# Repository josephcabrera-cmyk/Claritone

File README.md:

# Claritone

A head-mounted navigation aid for visually impaired users. Time-of-flight (ToF) sensors measure how far away obstacles are, and the device turns that distance into audio cues. The full design adds camera-based object detection and spatial audio. [Status at the showcase](#status-at-the-showcase) covers what actually ran.

Developed as a senior design project (ESE440/ESE441) at Stony Brook University, Fall 2025 – Spring 2026.

## Status at the showcase

**What ran:** the front VL53L7CX sensor drove an audio tone through both speakers. Closer obstacles sound higher, pulse faster and play louder. The user can pick one of three sensitivity ranges (0.3, 0.8 or 1.5 m) and three tone presets, and set volume or mute with the scroll wheel. This is [`firmware/Claritone_L7_Audio`](firmware/Claritone_L7_Audio).

**Designed but not finished:**

- **Side and rear sensors:** the firmware supports four sensors, but only the front one came online.
- **Spatial audio:** Sola's engine (panning, head shadow and interaural delay) is ported to the board in [`firmware/Claritone_Main`](firmware/Claritone_Main). With only the front sensor working, it had no direction to place a sound in.
- **Object detection:** the camera and computer vision work was developed separately in the [team repository](https://github.com/Niefr1/Blindsight-Claritone-Senior-Design) and wasn't combined with the ToF and audio firmware.
- **Battery-saving polling:** the plan was to run every sensor at a low rate and switch the front sensor to high-rate ranging when the camera flags a target.

## System design

The full design runs object detection on the STM32N6's Neural-ART NPU and pairs it with multizone ToF ranging:

1. A pre-trained model from ST's Model Zoo flags a region of interest in the camera frame.
2. The ToF sensors measure how far away that object is.
3. A spatial audio engine places a tone in the obstacle's direction, using equal-power panning, interaural time delay and distance attenuation.

## Hardware

**Custom PCB (Claritone Main Board)**

| Parameter | Value |
|---|---|
| Dimensions | 110 mm x 41.5 mm |
| Layer count | 4-layer FR-4 |
| MCU | STM32N657X0H3Q (Cortex-M55 + Neural-ART NPU, VFBGA-264) |
| ToF sensors | 1x VL53L7CX on-board + 3x SATEL-VL53L7CX breakouts via JST-GH |
| Camera | Arducam IMX335 via 15-pin MIPI CSI FPC connector |
| Audio output | 2x MAX98357A I2S Class-D amplifiers (stereo) |
| Power | 2x 3000 mAh LiPo cells in parallel, MCP73831T charge management, TPS62132 buck (3.3V), TPS7A2018 LDO (1.8V) |
| Protection | Battery reverse-polarity P-MOSFET (DMG2301L), resettable polyfuse (MF-PSMF075X), SD05 TVS diode, USBLC6-2SC6 ESD protection on Micro-USB |
| Charging | Micro-USB (power only) |
| Storage | MicroSD via SDMMC1 |
| Debug | STLINK-V3MINIE via STDC14 header (SWD + VCP) |
| Fabrication | JLCPCB (4-layer, ENIG finish) |

### Schematic

Full schematic PDF: [Claritone_Schematic.pdf](hardware/schematic/Claritone_Schematic.pdf)

### PCB Layout

Full layout PDFs: [Top](hardware/schematic/Claritone_PCB_TOP.pdf) | [Bottom](hardware/schematic/Claritone_PCB_BOTTOM.pdf)

### Design files

The EAGLE 9.7 sources are [`Claritone_Main.sch`](hardware/source/Claritone_Main.sch) and [`Claritone_Main.brd`](hardware/source/Claritone_Main.brd). They open in Autodesk EAGLE 9.7 or later and in Fusion Electronics.

### Bill of materials

[`hardware/bom/claritone-bom.csv`](hardware/bom/claritone-bom.csv) lists every part with a one-line design note ([`.xlsx`](hardware/bom/claritone-bom.xlsx) version).

## Firmware

[`firmware/`](firmware) holds one STM32CubeIDE project per bring-up step, from a pin-toggle test (L0) to the combined program (L8), plus `Claritone_Main`. L7 is the showcase build. [`firmware/README.md`](firmware/README.md) explains what each project does and how to build it.

[`prototypes/spatial-audio`](prototypes/spatial-audio) is Sola's desktop prototype of the spatial audio engine.

## Folder Structure

```
Claritone/
├── firmware/                 # STM32N657 sources and .ioc files
│   ├── Claritone_L0_Blinky/  # bring-up steps L0–L8, one project each
│   ├── ...
│   ├── Claritone_L7_Audio/   # showcase build
│   ├── Claritone_L8_Integration/
│   ├── Claritone_Main/       # spatial audio engine and UI
│   └── claritone-board.ioc   # board pin and peripheral configuration
├── prototypes/
│   └── spatial-audio/        # desktop spatial audio prototype
├── hardware/
│   ├── source/               # EAGLE schematic and board files
│   ├── schematic/            # schematic and layout PDFs and images
│   └── bom/                  # bill of materials
├── docs/
│   └── images/               # photo, renders, block diagram
└── README.md
```

## Building and Flashing

### Requirements
- STM32CubeMX and STM32CubeIDE
- STM32CubeProgrammer (CLI recommended for STM32N6)
- STLINK-V3MINIE debugger (firmware V3J17M10 or later)

### Steps
1. Generate each project's code from its `.ioc` in STM32CubeMX, then add ST's VL53L7CX ULD driver ([details](firmware/README.md#building))
2. Build the FSBL sub-project first
3. Build the Appli sub-project
4. Flash via SWD using STM32CubeProgrammer CLI

> **Note:** The STM32N657 requires dev boot mode (BOOT1 high) for SRAM write access and debug. On the custom PCB, DIP switch SW1 sets BOOT0 and BOOT1. BOOT1 is PA6, with a 10 kΩ pulldown (R46).

## Team

Built by a three-person team at Stony Brook University:

- **[Joseph Cabrera](https://github.com/josephcabrera-cmyk)**: schematic and 4-layer PCB design, board bring-up, ToF sensing architecture, the distance-to-tone mapping in the showcase build, and enclosure design
- **Sola**: the spatial audio engine
- **Joseph** and **Sola**: firmware
- **Felix** and **Sola**: computer vision model selection and deployment on the Neural-ART NPU

The full project, including the computer vision work, is in the [team repository](https://github.com/Niefr1/Blindsight-Claritone-Senior-Design).

## License

This project was developed for academic purposes. The VL53L7CX ULD driver (STSW-IMG036) is not included in this repository due to ST redistribution restrictions. ST's HAL and CMSIS are left out too, since STM32CubeMX regenerates them from each `.ioc`.

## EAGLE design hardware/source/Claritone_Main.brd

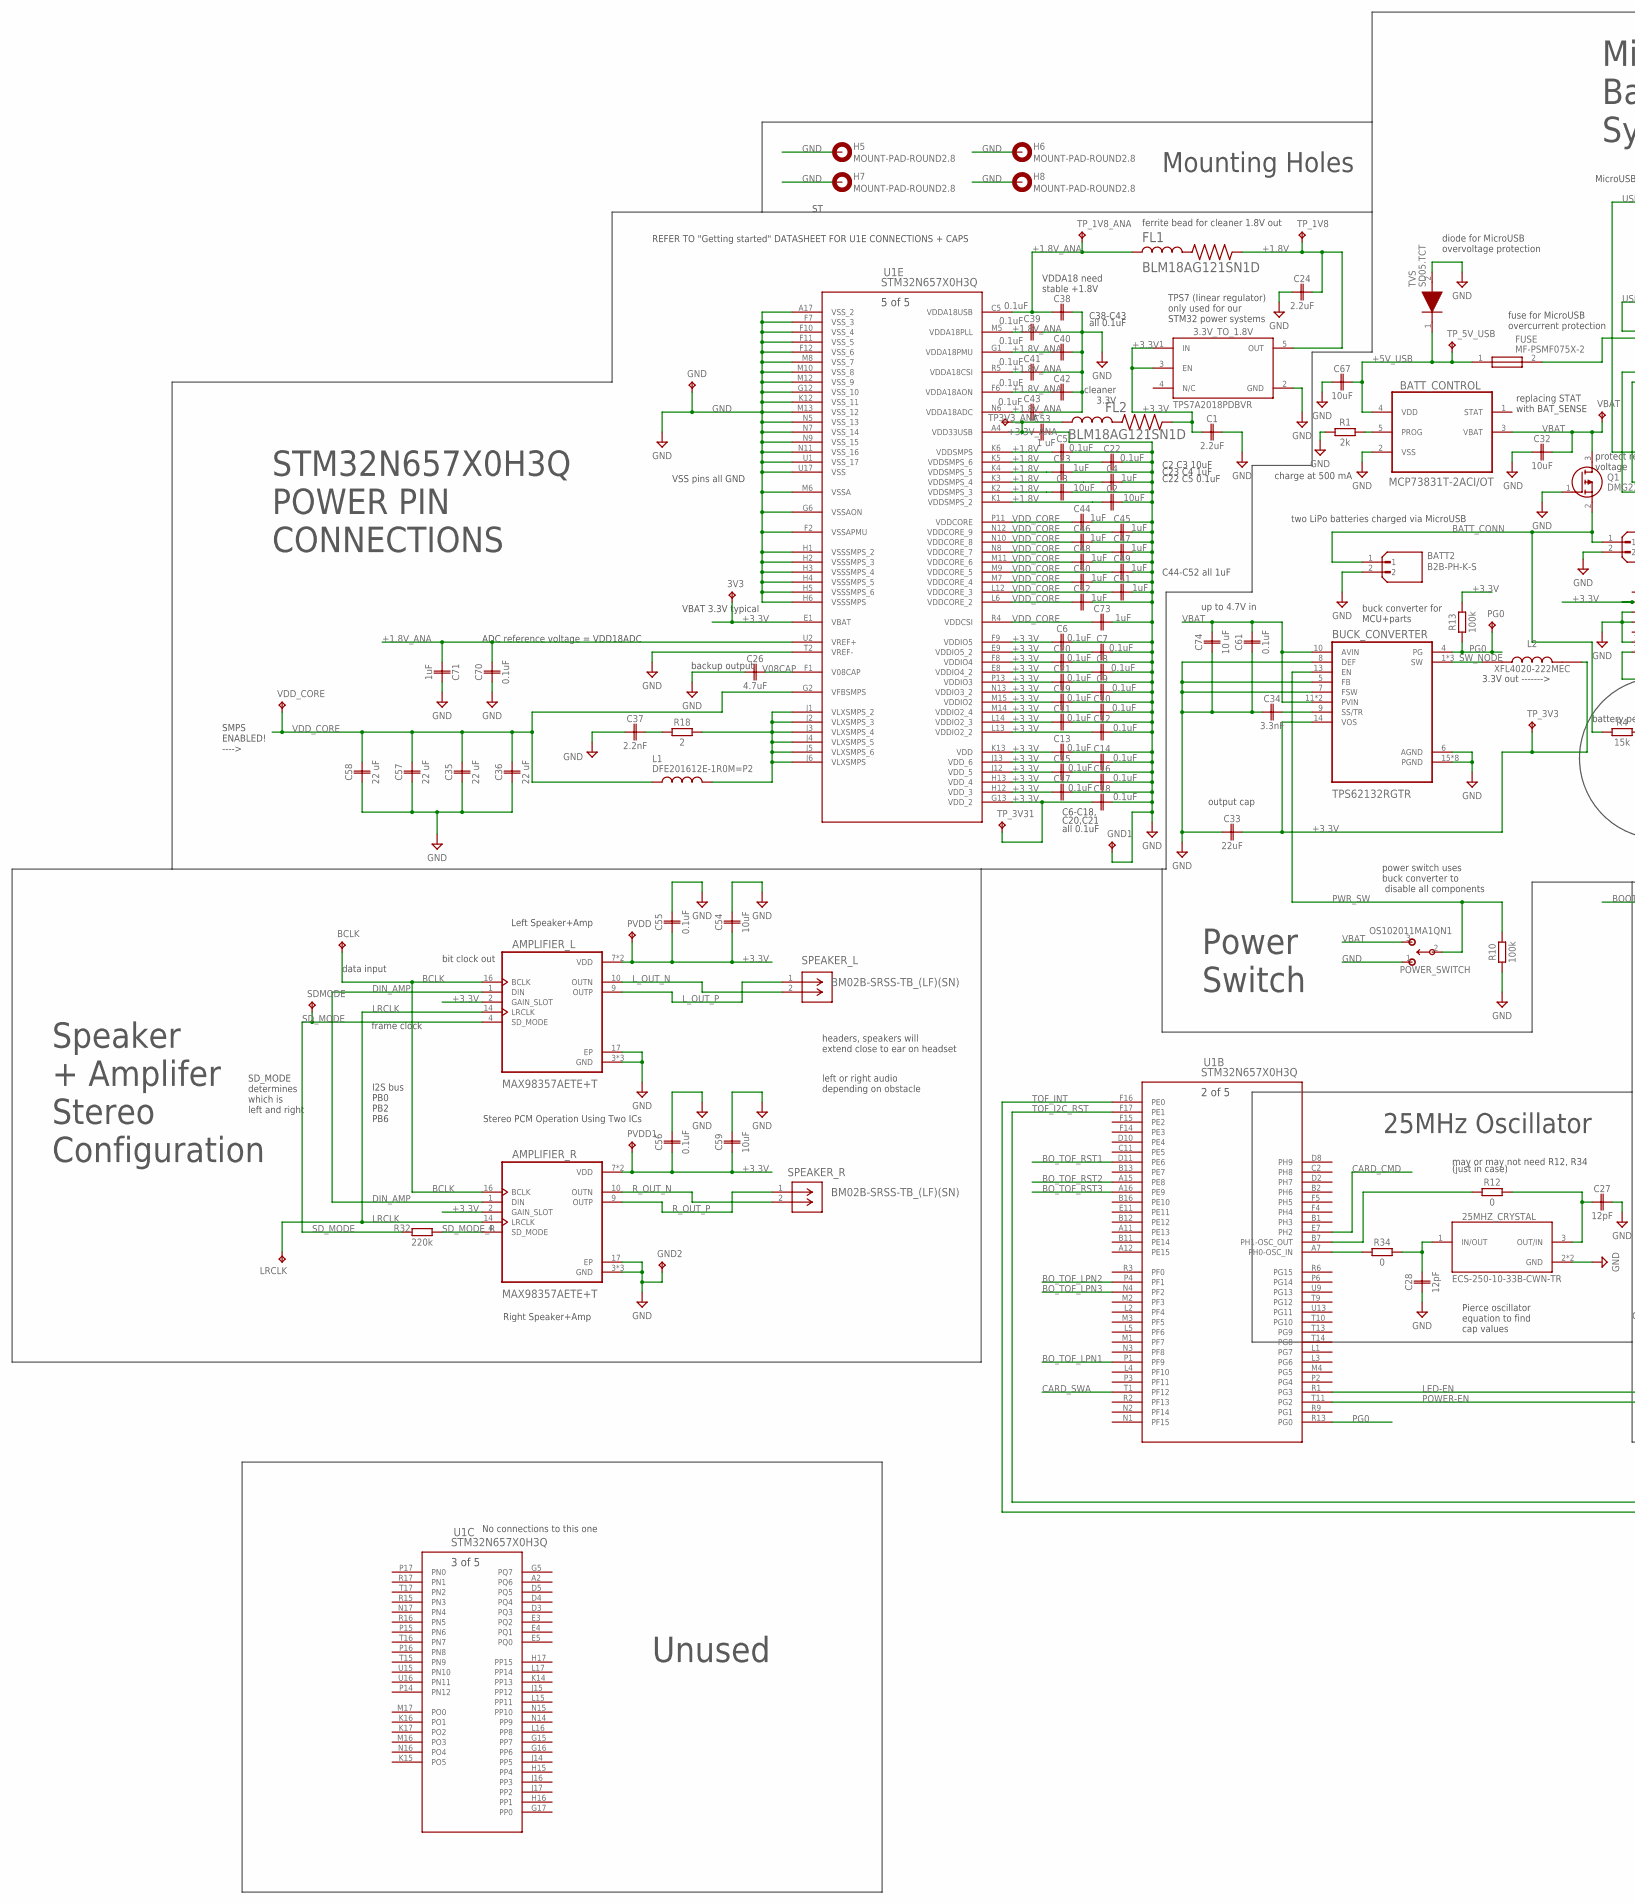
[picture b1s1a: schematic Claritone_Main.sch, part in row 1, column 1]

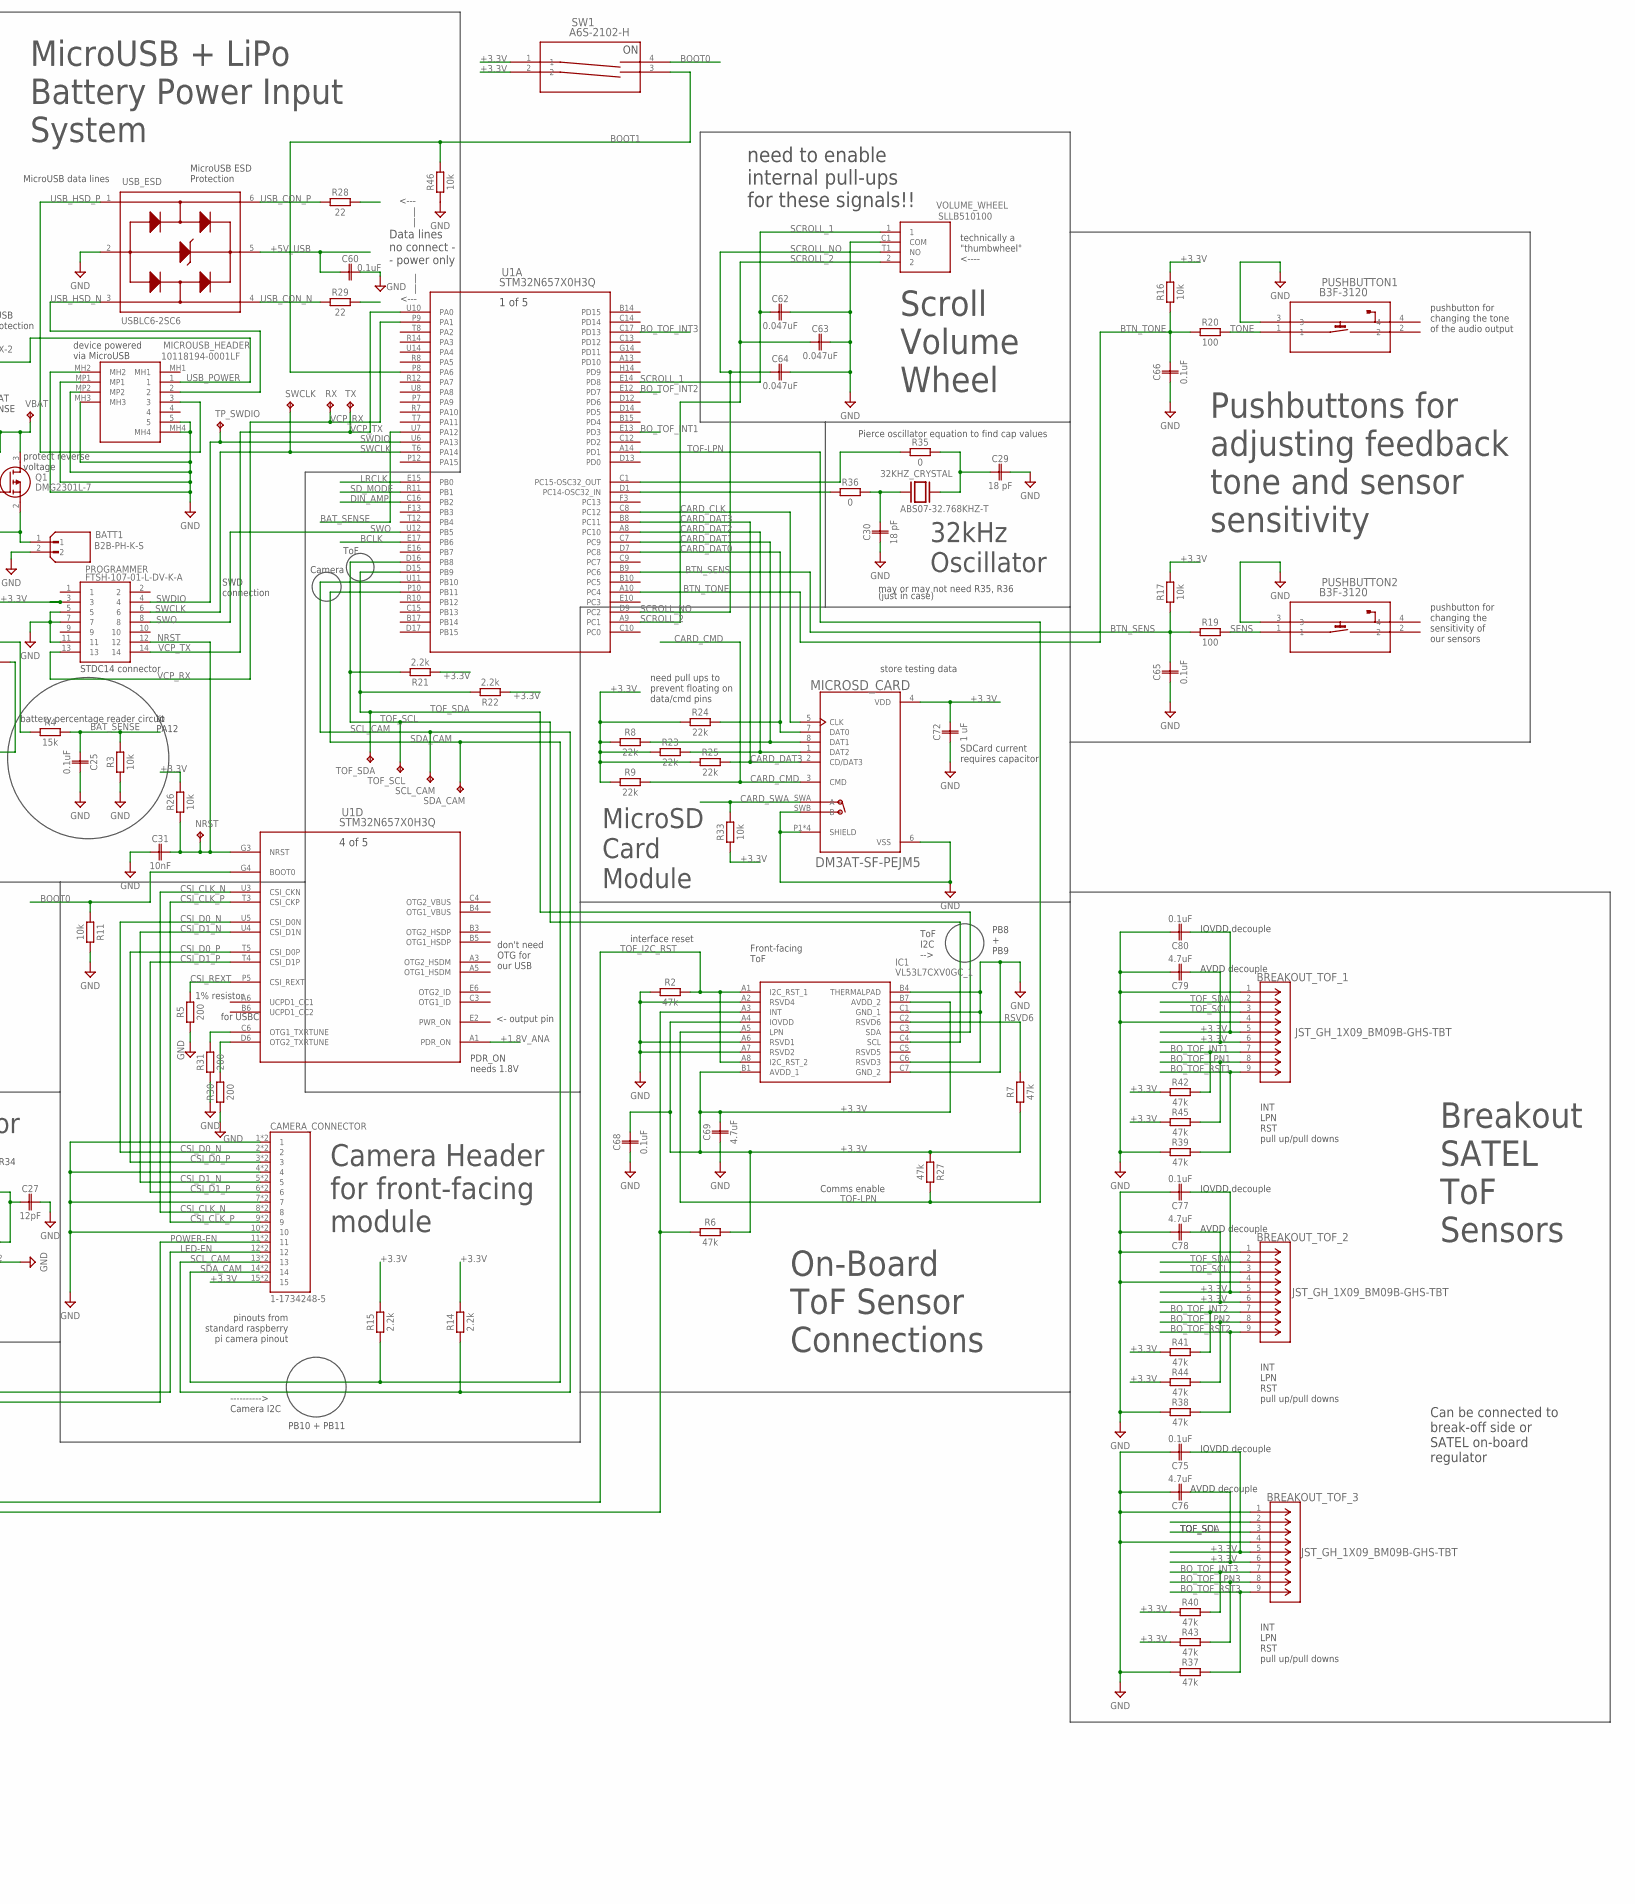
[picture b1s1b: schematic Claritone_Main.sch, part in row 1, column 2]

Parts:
3.3V_TO_1.8V: TPS7A2018PDBVR; SOT95P280X145-5N(3)
3V3: TPPAD1-13Y; P1-13Y
25MHZ_CRYSTAL: ECS-250-10-33B-CWN-TR; XTAL_ECS-250-10-33B-CWN-TR
32KHZ_CRYSTAL: ABS07-32.768KHZ-T; XTAL_ABS07-32.768KHZ-T
AMPLIFIER_L: MAX98357AETE+T; QFN50P300X300X80-17N
AMPLIFIER_R: MAX98357AETE+T; QFN50P300X300X80-17N
BATT1, BATT2: B2B-PH-K-S; JST_B2B-PH-K-S
BATT_CONTROL: MCP73831T-2ACI/OT; SOT95P280X145-5N(1)
BCLK: TPTP06R; TP06R
BREAKOUT_TOF_1, BREAKOUT_TOF_2, BREAKOUT_TOF_3: JST_GH_1X09_BM09B-GHS-TBT; CONN_BM09B-GHS-TBT_JST
BUCK_CONVERTER: TPS62132RGTR; QFN50P300X300X100-17N
C1, C24: 2.2uF; CAPC1005X60
C2, C3, C32, C54, C59, C67: 10uF; CAPC1608X85
C4, C23, C44, C45, C46, C47, C48, C49, C50, C51, C52, C71, C73: 1uF; CAPC1005X60
C5, C6, C7, C8, C9, C10, C11, C12, C13, C14, C15, C16, C17, C18, C19, C20, C21, C22, C25, C38, C39, C40, C41, C42, C43, C55, C56, C60, C61, C65, C66, C68, C70, C75, C77, C80: 0.1uF; CAPC1005X60
C26: 4.7uF; CAPC1005X60
C27, C28: 12pF; CAPC1005X60
C29, C30: 18 pF; CAPC1005X60
C31: 10nF; CAPC1005X60
C33: 22uF; CAPC1608X85
C34: 3.3nF; CAPC1005X60
C35, C36, C57, C58: 22 uF; CAPC1608X85
C37: 2.2nF; CAPC1005X60
C53, C72: 1 uF; CAPC1005X60
C62, C63, C64: 0.047uF; CAPC1005X60
C69, C76, C78, C79: 4.7uF; CAPC1608X85
C74: 10 uF; CAPC1608X85
CAMERA_CONNECTOR: 1-1734248-5; TE_1-1734248-5
FL1, FL2: BLM18AG121SN1D; BEADC1608X95N
FUSE: MF-PSMF075X-2; MFPSMF075X2
GND: TPPAD1-13Y; P1-13Y
GND1, GND2: TPTP08R; TP08R
H5, H6, H7, H8: MOUNT-PAD-ROUND2.8; 2,8-PAD
IC1: VL53L7CXV0GC_1; VL53L7CXV0GC1
L1: DFE201612E-1R0M=P2; INDC2016X120N
L2: XFL4020-222MEC; IND_XFL4020-222MEC
LRCLK: TPTP06R; TP06R
MICROSD_CARD: DM3AT-SF-PEJM5; HRS_DM3AT-SF-PEJM5
MICROUSB_HEADER: 10118194-0001LF; 101181940001LF
NRST: TPTP06R; TP06R
PG0: TPTP06R; TP06R
POWER_SWITCH: OS102011MA1QN1; SWITCH_11MA1QN1
PROGRAMMER: FTSH-107-01-L-DV-K-A; FTSH-107-XX-YYY-DV-K-A
PUSHBUTTON1, PUSHBUTTON2: B3F-3120; SW_B3F-3120_OMR
PVDD, PVDD1: TPTP06R; TP06R
Q1: DMG2301L-7; SOT96P240X115-3N
R1: 2k; RESC1005X40
R2, R6, R7, R27, R37, R38, R39, R40, R41, R42, R43, R44, R45: 47k; RESC1005X40
R3, R11, R16, R17, R26, R33, R46: 10k; RESC1005X40
R4: 15k; RESC1005X40
R5, R30, R31: 200; RESC1005X40
R8, R9, R23, R24, R25: 22k; RESC1005X40
R10, R13: 100k; RESC1005X40
R12, R34, R35, R36: 0; RESC1005X40
R14, R15, R21, R22: 2.2k; RESC1005X40
R18: 2; RESC1005X40
R19, R20: 100; RESC1005X40
R28, R29: 22; RESC1005X40
R32: 220k; RESC1005X40
RX: TPTP06R; TP06R
SCL_CAM: TPTP06R; TP06R
SDA_CAM: TPTP06R; TP06R
SDMODE: TPTP06R; TP06R
SPEAKER_L: BM02B-SRSS-TB_(LF)(SN); CONN_BM02B-SRSS-TB_JST
SPEAKER_R: BM02B-SRSS-TB_(LF)(SN); CONN_BM02B-SRSS-TB_JST
SW1: A6S-2102-H; SW_A6S-2102-H_OMR
SWCLK: TPTP06R; TP06R
TOF_SCL: TPTP06R; TP06R
TOF_SDA: TPTP06R; TP06R
TP3V3_ANA: TPTP06R; TP06R
TP_1V8, TP_1V8_ANA, TP_3V3, TP_3V31, TP_5V_USB: TPTP06R; TP06R
TP_SWDIO: TPTP06R; TP06R
TVS: SD05.TCT; SOD2513X110N
TX: TPTP06R; TP06R
U1: STM32N657X0H3Q; VFBGA264_14X14_STM
USB_ESD: USBLC6-2SC6; SOT95P280X145-6N
VBAT: TPTP06R; TP06R
VDD_CORE: TPTP06R; TP06R
VOLUME_WHEEL: SLLB510100

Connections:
+1.8V: 3.3V_TO_1.8V.5 (OUT), C2.1, C3.1, C4.1, C5.1, C22.1, C23.1, C24.2, FL1.2, TP_1V8.TP, U1.K1 (VDDSMPS_2), U1.K2 (VDDSMPS_3), U1.K3 (VDDSMPS_4), U1.K4 (VDDSMPS_5), U1.K5 (VDDSMPS_6), U1.K6 (VDDSMPS)
+1.8V_ANA: C38.1, C39.1, C40.1, C41.1, C42.1, C43.1, C70.2, C71.1, FL1.1, TP_1V8_ANA.TP, U1.A1 (PDR_ON), U1.C5 (VDDA18USB), U1.F6 (VDDA18AON), U1.G1 (VDDA18PMU), U1.M5 (VDDA18PLL), U1.N6 (VDDA18ADC), U1.R5 (VDDA18CSI), U1.U2 (VREF+)
+3.3V: 3.3V_TO_1.8V.1 (IN), 3.3V_TO_1.8V.3 (EN), 3V3.TP, AMPLIFIER_L.2 (GAIN_SLOT), AMPLIFIER_L.7 (VDD), AMPLIFIER_L.8 (VDD), AMPLIFIER_R.2 (GAIN_SLOT), AMPLIFIER_R.7 (VDD), AMPLIFIER_R.8 (VDD), BREAKOUT_TOF_1.5, BREAKOUT_TOF_1.6, BREAKOUT_TOF_2.5, BREAKOUT_TOF_2.6, BREAKOUT_TOF_3.5, BREAKOUT_TOF_3.6, BUCK_CONVERTER.14 (VOS), C1.1, C6.1, C7.1, C8.1, C9.1, C10.1, C11.1, C12.1, C13.1, C14.1, C15.1, C16.1, C17.1, C18.1, C19.1, C20.1, C21.1, C33.2, C54.1, C55.1, C56.1, C59.1, C68.2, C69.2, C72.2, C75.1, C76.1, C77.1, C78.1, C79.1, C80.1, CAMERA_CONNECTOR.15, CAMERA_CONNECTOR.15_1 (15), FL2.2, IC1.A4 (IOVDD), IC1.B1 (AVDD_1), IC1.B7 (AVDD_2), L2.2, MICROSD_CARD.4 (VDD), PROGRAMMER.3, PVDD.TP, PVDD1.TP, R6.2, R7.1, R8.1, R9.1, R13.2, R14.2, R15.2, R16.2, R17.2, R21.1, R22.1, R23.1, R24.1, R25.1, R26.2, R27.1, R33.1, R40.1, R41.1, R42.1, R43.1, R44.1, R45.1, SW1.1, SW1.2, TP_3V3.TP, TP_3V31.TP, U1.E1 (VBAT), U1.E8 (VDDIO4_2), U1.E9 (VDDIO5_2), U1.F8 (VDDIO4), U1.F9 (VDDIO5), U1.G13 (VDD_2), U1.H12 (VDD_3), U1.H13 (VDD_4), U1.J12 (VDD_5), U1.J13 (VDD_6), U1.K13 (VDD), U1.L13 (VDDIO2_2), U1.L14 (VDDIO2_3), U1.M14 (VDDIO2_4), U1.M15 (VDDIO2), U1.N13 (VDDIO3_2), U1.P13 (VDDIO3)
+3.3V_ANA: C53.1, FL2.1, TP3V3_ANA.TP, U1.A4 (VDD33USB)
+5V_USB: BATT_CONTROL.4 (VDD), C60.1, C67.2, FUSE.1, TP_5V_USB.TP, TVS.1 (K), USB_ESD.5 (VBUS)
BATT_CONN: BATT1.1, BATT2.1, Q1.2 (S), R4.1
BAT_SENSE: C25.1, R3.2, R4.2, U1.U7 (PA12)
BCLK: AMPLIFIER_L.16 (BCLK), AMPLIFIER_R.16 (BCLK), BCLK.TP, U1.E17 (PB6)
BOOT0: R11.1, SW1.4, U1.G4 (BOOT0)
BOOT1: R46.2, SW1.3, U1.P8 (PA6)
BO_TOF_INT1: BREAKOUT_TOF_1.7, R42.2, U1.E13 (PD3)
BO_TOF_INT2: BREAKOUT_TOF_2.7, R41.2, U1.E12 (PD7)
BO_TOF_INT3: BREAKOUT_TOF_3.7, R40.2, U1.C17 (PD13)
BO_TOF_LPN1: BREAKOUT_TOF_1.8, R45.2, U1.P1 (PF9)
BO_TOF_LPN2: BREAKOUT_TOF_2.8, R44.2, U1.P4 (PF1)
BO_TOF_LPN3: BREAKOUT_TOF_3.8, R43.2, U1.N4 (PF2)
BO_TOF_RST1: BREAKOUT_TOF_1.9, R39.2, U1.D11 (PE6)
BO_TOF_RST2: BREAKOUT_TOF_2.9, R38.2, U1.A15 (PE8)
BO_TOF_RST3: BREAKOUT_TOF_3.9, R37.2, U1.A16 (PE9)
BTN_SENS: C65.2, R17.1, R19.1, U1.B9 (PC6)
BTN_TONE: C66.2, R16.1, R20.1, U1.A10 (PC4)
CARD_CLK: MICROSD_CARD.5 (CLK), U1.C8 (PC12)
CARD_CMD: MICROSD_CARD.3 (CMD), R9.2, U1.E7 (PH2)
CARD_DAT0: MICROSD_CARD.7 (DAT0), R24.2, U1.D7 (PC8)
CARD_DAT1: MICROSD_CARD.8 (DAT1), R8.2, U1.C7 (PC9)
CARD_DAT2: MICROSD_CARD.1 (DAT2), R23.2, U1.A8 (PC10)
CARD_DAT3: MICROSD_CARD.2 (CD/DAT3), R25.2, U1.B8 (PC11)
CARD_SWA: MICROSD_CARD.SWA (A), R33.2, U1.T1 (PF12)
CSI_CLK_N: CAMERA_CONNECTOR.8, CAMERA_CONNECTOR.8_1 (8), U1.U3 (CSI_CKN)
CSI_CLK_P: CAMERA_CONNECTOR.9, CAMERA_CONNECTOR.9_1 (9), U1.T3 (CSI_CKP)
CSI_D0_N: CAMERA_CONNECTOR.2, CAMERA_CONNECTOR.2_1 (2), U1.U5 (CSI_D0N)
CSI_D0_P: CAMERA_CONNECTOR.3, CAMERA_CONNECTOR.3_1 (3), U1.T5 (CSI_D0P)
CSI_D1_N: CAMERA_CONNECTOR.5, CAMERA_CONNECTOR.5_1 (5), U1.U4 (CSI_D1N)
CSI_D1_P: CAMERA_CONNECTOR.6, CAMERA_CONNECTOR.6_1 (6), U1.T4 (CSI_D1P)
CSI_REXT: R5.2, U1.P5 (CSI_REXT)
DIN_AMP: AMPLIFIER_L.1 (DIN), AMPLIFIER_R.1 (DIN), U1.C16 (PB2)
GND: 3.3V_TO_1.8V.2 (GND), 25MHZ_CRYSTAL.2 (GND), 25MHZ_CRYSTAL.4 (GND), AMPLIFIER_L.3 (GND), AMPLIFIER_L.11 (GND), AMPLIFIER_L.15 (GND), AMPLIFIER_L.17 (EP), AMPLIFIER_R.3 (GND), AMPLIFIER_R.11 (GND), AMPLIFIER_R.15 (GND), AMPLIFIER_R.17 (EP), BATT1.2, BATT2.2, BATT_CONTROL.2 (VSS), BREAKOUT_TOF_1.1, BREAKOUT_TOF_1.4, BREAKOUT_TOF_2.1, BREAKOUT_TOF_2.4, BREAKOUT_TOF_3.1, BREAKOUT_TOF_3.4, BUCK_CONVERTER.5 (FB), BUCK_CONVERTER.6 (AGND), BUCK_CONVERTER.7 (FSW), BUCK_CONVERTER.8 (DEF), BUCK_CONVERTER.15 (PGND), BUCK_CONVERTER.16 (PGND), BUCK_CONVERTER.17 (PGND), BUCK_CONVERTER.18 (PGND), BUCK_CONVERTER.19 (PGND), BUCK_CONVERTER.20 (PGND), BUCK_CONVERTER.21 (PGND), BUCK_CONVERTER.22 (PGND), C1.2, C2.2, C3.2, C4.2, C5.2, C6.2, C7.2, C8.2, C9.2, C10.2, C11.2, C12.2, C13.2, C14.2, C15.2, C16.2, C17.2, C18.2, C19.2, C20.2, C21.2, C22.2, C23.2, C24.1, C25.2, C26.1, C27.2, C28.1, C29.2, C30.1, C31.1, C32.1, C33.1, C34.1, C35.1, C36.1, C37.1, C38.2, C39.2, C40.2, C41.2, C42.2, C43.2, C44.2, C45.2, C46.2, C47.2, C48.2, C49.2, C50.2, C51.2, C52.2, C53.2, C54.2, C55.2, C56.2, C57.1, C58.1, C59.2, C60.2, C61.1, C62.2, C63.2, C64.2, C65.1, C66.1, C67.1, C68.1, C69.1, C70.1, C71.2, C72.1, C73.2, C74.1, C75.2, C76.2, C77.2, C78.2, C79.2, C80.2, CAMERA_CONNECTOR.1, CAMERA_CONNECTOR.1_1 (1), CAMERA_CONNECTOR.4, CAMERA_CONNECTOR.4_1 (4), CAMERA_CONNECTOR.7, CAMERA_CONNECTOR.7_1 (7), CAMERA_CONNECTOR.10, CAMERA_CONNECTOR.10_1 (10), GND.TP, GND1.TP, GND2.TP, H5.B2,8, H6.B2,8, H7.B2,8, H8.B2,8, IC1.A2 (RSVD4), IC1.A6 (RSVD1), IC1.A7 (RSVD2), IC1.B4 (THERMALPAD), IC1.C1 (GND_1), IC1.C6 (RSVD3), IC1.C7 (GND_2), MICROSD_CARD.6 (VSS), MICROSD_CARD.P1 (SHIELD), MICROSD_CARD.P2 (SHIELD), MICROSD_CARD.P3 (SHIELD), MICROSD_CARD.P4 (SHIELD), MICROSD_CARD.SWB (B), MICROUSB_HEADER.5, MICROUSB_HEADER.MH2, MICROUSB_HEADER.MH3, MICROUSB_HEADER.MH4, MICROUSB_HEADER.MP1, MICROUSB_HEADER.MP2, POWER_SWITCH.1, PROGRAMMER.5, PROGRAMMER.7, PROGRAMMER.11, PUSHBUTTON1.3, PUSHBUTTON2.3, Q1.1 (G), R1.1, R2.1, R3.1, R5.1, R10.1, R11.2, R30.1, R31.1, R37.1, R38.1, R39.1, R46.1, TVS.2 (A), U1.A17 (VSS_2), U1.F2 (VSSAPMU), U1.F7 (VSS_3), U1.F10 (VSS_4), U1.F11 (VSS_5), U1.F12 (VSS_6), U1.G6 (VSSAON), U1.G12 (VSS_10), U1.H1 (VSSSMPS_2), U1.H2 (VSSSMPS_3), U1.H3 (VSSSMPS_4), U1.H4 (VSSSMPS_5), U1.H5 (VSSSMPS_6), U1.H6 (VSSSMPS), U1.K12 (VSS_11), U1.M6 (VSSA), U1.M8 (VSS_7), U1.M10 (VSS_8), U1.M12 (VSS_9), U1.M13 (VSS_12), U1.N5 (VSS_13), U1.N7 (VSS_14), U1.N9 (VSS_15), U1.N11 (VSS_16), U1.T2 (VREF-), U1.U1 (VSS_17), U1.U17 (VSS), USB_ESD.2 (GND), VOLUME_WHEEL.C1 (COM)
LED-EN: CAMERA_CONNECTOR.12, CAMERA_CONNECTOR.12_1 (12), U1.R1 (PG3)
LRCLK: AMPLIFIER_L.14 (LRCLK), AMPLIFIER_R.14 (LRCLK), LRCLK.TP, U1.E15 (PB0)
L_OUT_N: AMPLIFIER_L.10 (OUTN), SPEAKER_L.2
L_OUT_P: AMPLIFIER_L.9 (OUTP), SPEAKER_L.1
unnamed: C37.2, R18.1
unnamed: BATT_CONTROL.5 (PROG), R1.2
unnamed: BUCK_CONVERTER.9 (SS/TR), C34.2
unnamed: 25MHZ_CRYSTAL.3 (OUT/IN), C27.1, R12.2
unnamed: R34.1, U1.A7 (PH0-OSC_IN)
unnamed: 25MHZ_CRYSTAL.1 (IN/OUT), C28.2, R34.2
unnamed: R36.1, U1.D1 (PC14-OSC32_IN)
unnamed: R35.1, U1.C1 (PC15-OSC32_OUT)
unnamed: 32KHZ_CRYSTAL.2, C29.1, R35.2
unnamed: 32KHZ_CRYSTAL.1, C30.2, R36.2
unnamed: R12.1, U1.B7 (PH1-OSC_OUT)
NRST: C31.2, NRST.TP, PROGRAMMER.12, R26.1, U1.G3 (NRST)
OTG1_TXR: R31.2, U1.C6 (OTG1_TXRTUNE)
OTG2_TXR: R30.2, U1.D6 (OTG2_TXRTUNE)
PG0: BUCK_CONVERTER.4 (PG), PG0.TP, R13.1, U1.R13 (PG0)
POWER-EN: CAMERA_CONNECTOR.11, CAMERA_CONNECTOR.11_1 (11), U1.T11 (PG2)
PWR_SW: BUCK_CONVERTER.13 (EN), POWER_SWITCH.2, R10.2
RSVD6: IC1.C2 (RSVD6), R7.2
R_OUT_N: AMPLIFIER_R.10 (OUTN), SPEAKER_R.2
R_OUT_P: AMPLIFIER_R.9 (OUTP), SPEAKER_R.1
SCL_CAM: CAMERA_CONNECTOR.13, CAMERA_CONNECTOR.13_1 (13), R14.1, SCL_CAM.TP, U1.U11 (PB10)
SCROLL_1: C62.1, U1.E14 (PD8), VOLUME_WHEEL.1
SCROLL_2: C63.1, U1.A9 (PC1), VOLUME_WHEEL.2
SCROLL_NO: C64.1, U1.D9 (PC2), VOLUME_WHEEL.T1 (NO)
SDA_CAM: CAMERA_CONNECTOR.14, CAMERA_CONNECTOR.14_1 (14), R15.1, SDA_CAM.TP, U1.P10 (PB11)
SD_MODE: AMPLIFIER_L.4 (SD_MODE), R32.1, SDMODE.TP, U1.R11 (PB1)
SD_MODE_R: AMPLIFIER_R.4 (SD_MODE), R32.2
SENS: PUSHBUTTON2.1, R19.2
SWCLK: PROGRAMMER.6, SWCLK.TP, U1.T6 (PA14)
SWDIO: PROGRAMMER.4, TP_SWDIO.TP, U1.U6 (PA13)
SWO: PROGRAMMER.8, U1.U12 (PB5)
SW_NODE: BUCK_CONVERTER.1 (SW), BUCK_CONVERTER.2 (SW), BUCK_CONVERTER.3 (SW), L2.1
TOF-LPN: IC1.A5 (LPN), R27.2, U1.A14 (PD1)
TOF_I2C_RST: IC1.A1 (I2C_RST_1), IC1.A8 (I2C_RST_2), R2.2, U1.F17 (PE1)
TOF_INT: IC1.A3 (INT), R6.1, U1.F16 (PE0)
TOF_SCL: BREAKOUT_TOF_1.3, BREAKOUT_TOF_2.3, BREAKOUT_TOF_3.3, IC1.C4 (SCL), R21.2, TOF_SCL.TP, U1.D16 (PB8)
TOF_SDA: BREAKOUT_TOF_1.2, BREAKOUT_TOF_2.2, BREAKOUT_TOF_3.2, IC1.C3 (SDA), R22.2, TOF_SDA.TP, U1.D15 (PB9)
TONE: PUSHBUTTON1.1, R20.2
USB_CON_N: R29.1, USB_ESD.4 (I/O2_OUT)
USB_CON_P: R28.1, USB_ESD.6 (I/O1_OUT)
USB_HSD_N: MICROUSB_HEADER.2, USB_ESD.3 (I/O2_IN)
USB_HSD_P: MICROUSB_HEADER.3, USB_ESD.1 (I/O1_IN)
USB_POWER: FUSE.2, MICROUSB_HEADER.1
V08CAP: C26.2, U1.F1 (V08CAP)
VBAT: BATT_CONTROL.3 (VBAT), BUCK_CONVERTER.10 (AVIN), BUCK_CONVERTER.11 (PVIN), BUCK_CONVERTER.12 (PVIN), C32.2, C61.2, C74.2, POWER_SWITCH.3, Q1.3 (D), VBAT.TP
VCP_RX: PROGRAMMER.13, RX.TP, U1.P9 (PA1)
VCP_TX: PROGRAMMER.14, TX.TP, U1.U10 (PA0)
VDD_CORE: C35.2, C36.2, C44.1, C45.1, C46.1, C47.1, C48.1, C49.1, C50.1, C51.1, C52.1, C57.2, C58.2, C73.1, L1.1, U1.G2 (VFBSMPS), U1.L6 (VDDCORE_2), U1.L12 (VDDCORE_3), U1.M7 (VDDCORE_4), U1.M9 (VDDCORE_5), U1.M11 (VDDCORE_6), U1.N8 (VDDCORE_7), U1.N10 (VDDCORE_8), U1.N12 (VDDCORE_9), U1.P11 (VDDCORE), U1.R4 (VDDCSI), VDD_CORE.TP
VLXSMPS: L1.2, R18.2, U1.J1 (VLXSMPS_2), U1.J2 (VLXSMPS_3), U1.J3 (VLXSMPS_4), U1.J4 (VLXSMPS_5), U1.J5 (VLXSMPS_6), U1.J6 (VLXSMPS)

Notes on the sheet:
battery percentage reader circuit
ferrite bead for cleaner 1.8V out
No connections to this one
C44-C52 all 1uF
C6-C18, C20,C21 all 0.1uF
C2 C3 10uF C23 C4 1uF C22 C5 0.1uF
C38-C43 all 0.1uF
cleaner 3.3V
may or may not need R12, R34 (just in case)
VSS pins all GND
VBAT 3.3V typical
ADC reference voltage = VDD18ADC
REFER TO "Getting started" DATASHEET FOR U1E CONNECTIONS + CAPS
VDDA18 need stable +1.8V
TPS7 (linear regulator) only used for our STM32 power systems
PDR_ON needs 1.8V
backup output
SMPS ENABLED! ---->
replacing STAT with BAT_SENSE
fuse for MicroUSB overcurrent protection
diode for MicroUSB overvoltage protection
charge at 500 mA
device powered via MicroUSB
MicroUSB ESD Protection
two LiPo batteries charged via MicroUSB
MicroUSB data lines
to PA12
SWD connection
STDC14 connector
buck converter for MCU+parts
output cap
up to 4.7V in
3.3V out ------->
Stereo PCM Operation Using Two ICs
Left Speaker+Amp
Right Speaker+Amp
SD_MODE determines which is left and right
I2S bus PB0 PB2 PB6
left or right audio depending on obstacle
headers, speakers will extend close to ear on headset

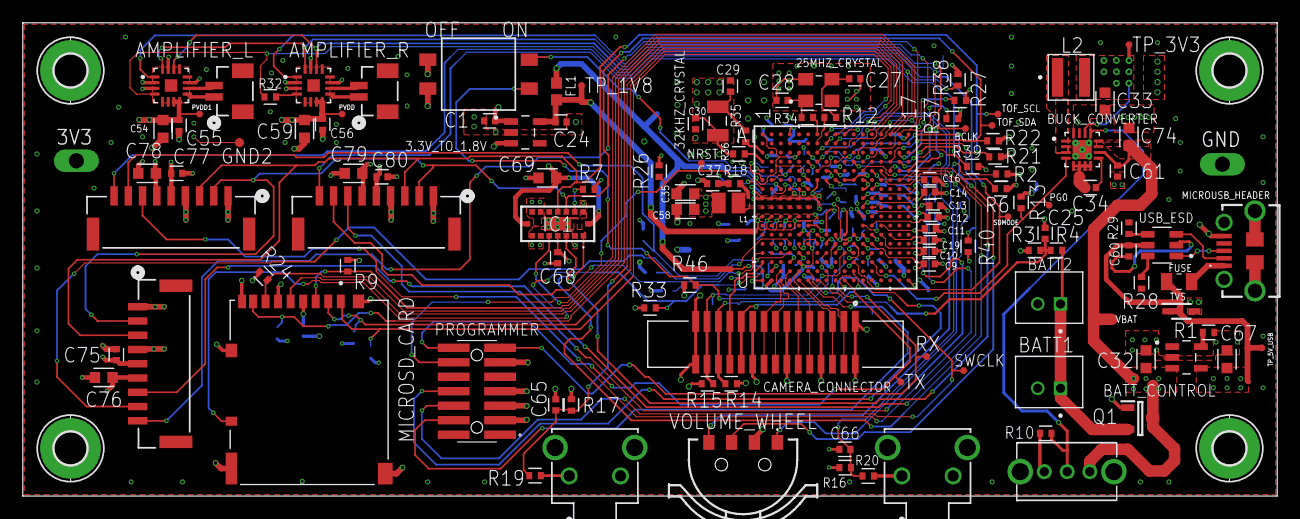
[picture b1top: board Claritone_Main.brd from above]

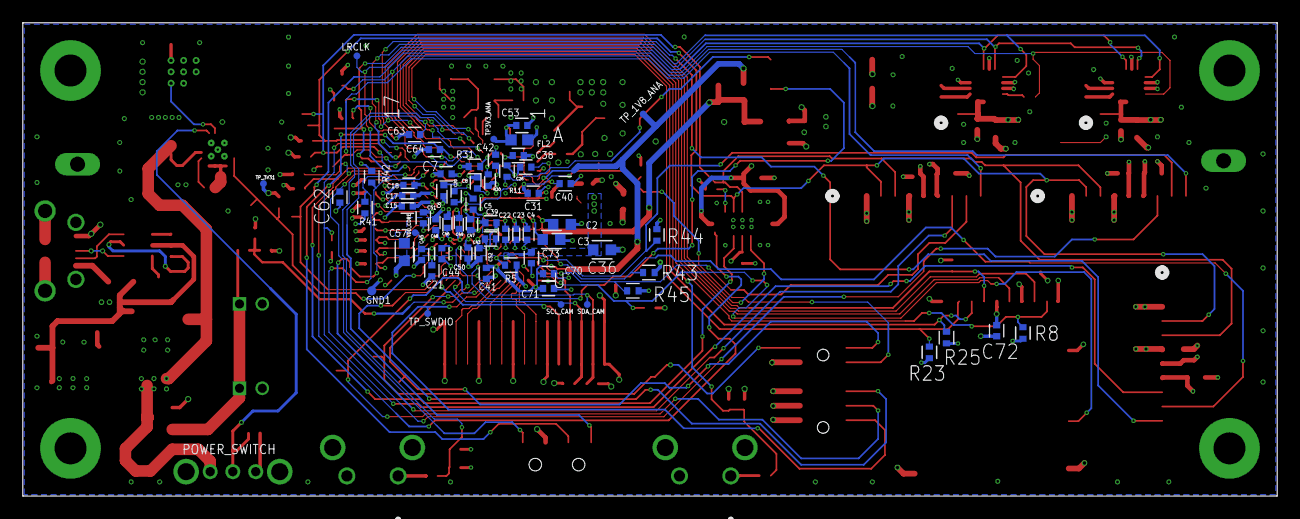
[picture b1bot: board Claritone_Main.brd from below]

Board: 4 copper layers, 110.0 x 41.5 mm, 190 parts (63 on the bottom side), 90 nets.

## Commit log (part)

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2026-04-13 readme

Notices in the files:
parts and their libraries:
COPYRIGHT: Copyright (C) 2026 Ultra Librarian. All rights reserved.
